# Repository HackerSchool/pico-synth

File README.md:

# pico-synth
The Pico-Synth Board v0.1 is the first version of a Raspberry Pi Pico based synthesizer, featuring an I2S DAC with line-out, a 2x8 switch matrix with individual LEDs, four rotary encoders with switches, an OLED screen, and an SD card slot for optional storage. This fist iteration of the board was designed with a focus on low cost and component availability.

## 📥 1. Clone the Repository & Initialize Submodules

```sh
git clone --recursive https://github.com/HackerSchool/pico-synth.git
cd pico-synth
```

If you already cloned without `--recursive`, initialize submodules manually:

```sh
git submodule update --init --recursive
```

## 📦 2. Install the Pico SDK and Pico Extras

### **Option 1: Install via Raspberry Pi Repo (Recommended on Raspberry Pi OS)**
```sh
sudo apt install cmake gcc-arm-none-eabi libnewlib-arm-none-eabi build-essential
```

### **Option 2: Manually Install (For Other Linux/Windows/macOS)**
#### **Clone & Set Up the Pico SDK**
```sh
mkdir -p ~/pico && cd ~/pico
git clone --recursive https://github.com/raspberrypi/pico-sdk.git
cd pico-sdk
git submodule update --init
```

#### **Clone & Set Up Pico Extras**
```sh
cd ~/pico
git clone --recursive https://github.com/raspberrypi/pico-extras.git
```

## 🌍 3. Set Environment Variables (Each Terminal Session)

Before building, set the paths so CMake can find the SDK and extras:

```sh
export PICO_SDK_PATH=~/pico/pico-sdk
export PICO_EXTRAS_PATH=~/pico/pico-extras
```

To make this **permanent**, add these lines to `~/.bashrc` or `~/.zshrc`:

```sh
echo 'export PICO_SDK_PATH=~/pico/pico-sdk' >> ~/.bashrc
echo 'export PICO_EXTRAS_PATH=~/pico/pico-extras' >> ~/.bashrc
source ~/.bashrc
```

## 🛠 4. Build the Project

1. **Create a Build Directory**
```sh
mkdir -p build && cd build
```

2. **Run CMake to Configure the Build**
```sh
cmake ..
```
if using ninja on windows:
```sh
cmake -G "Ninja" ..
```
3. **Compile the Code**
```sh
make -j$(nproc)
```
if using ninja on windows:
```sh
ninja
```
## 🔥 5. Flash to the Raspberry Pi Pico

### **Step 1: Put the Pico in Bootloader Mode**
- Hold down the **BOOTSEL** button on the Pico.
- Plug it into your computer via **USB**.
- It should appear as a **USB mass storage device** (RPI-RP2).

### **Step 2: Copy the `.uf2` Binary to the Pico**

Once built, the `pico-synth` binary (`.uf2` file) will be in `build/`:
```sh
cp build/pico-synth.uf2 /media/$USER/RPI-RP2/
```

The Pico will automatically reboot and start running the synthesizer!

---

## 🛠 Troubleshooting

- **"pico_sdk_import.cmake not found" error?**
  - Make sure `PICO_SDK_PATH` is set correctly.
  - Try running `source ~/.bashrc`.

- **No `*.uf2` file after `make`?**
  - Check the build log for errors.
  - Ensure `pico_enable_stdio_usb(${bin_name} 1)` is set in `CMakeLists.txt`.

---

## 📜 License
[GPLV3 License](LICENSE)

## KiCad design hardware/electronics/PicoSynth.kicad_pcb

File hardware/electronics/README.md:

# Pico Synth Hardware

The Pico-Synth Board v0.1 is the first version of the synthesizer, featuring a DAC with line-out, a 4x4 switch matrix with individual LEDs, four rotary encoders with switches, an OLED screen, and an SD card slot for optional storage. This fist iteration of the board was designed with a focus on low cost and component availability.

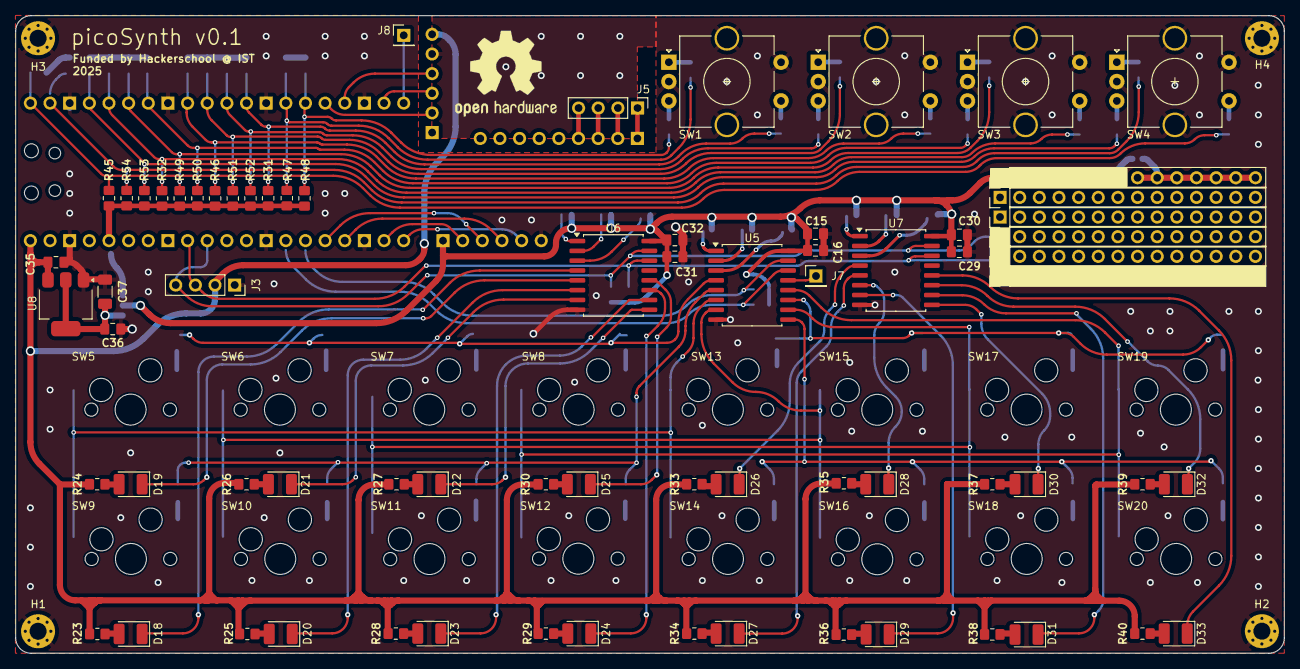
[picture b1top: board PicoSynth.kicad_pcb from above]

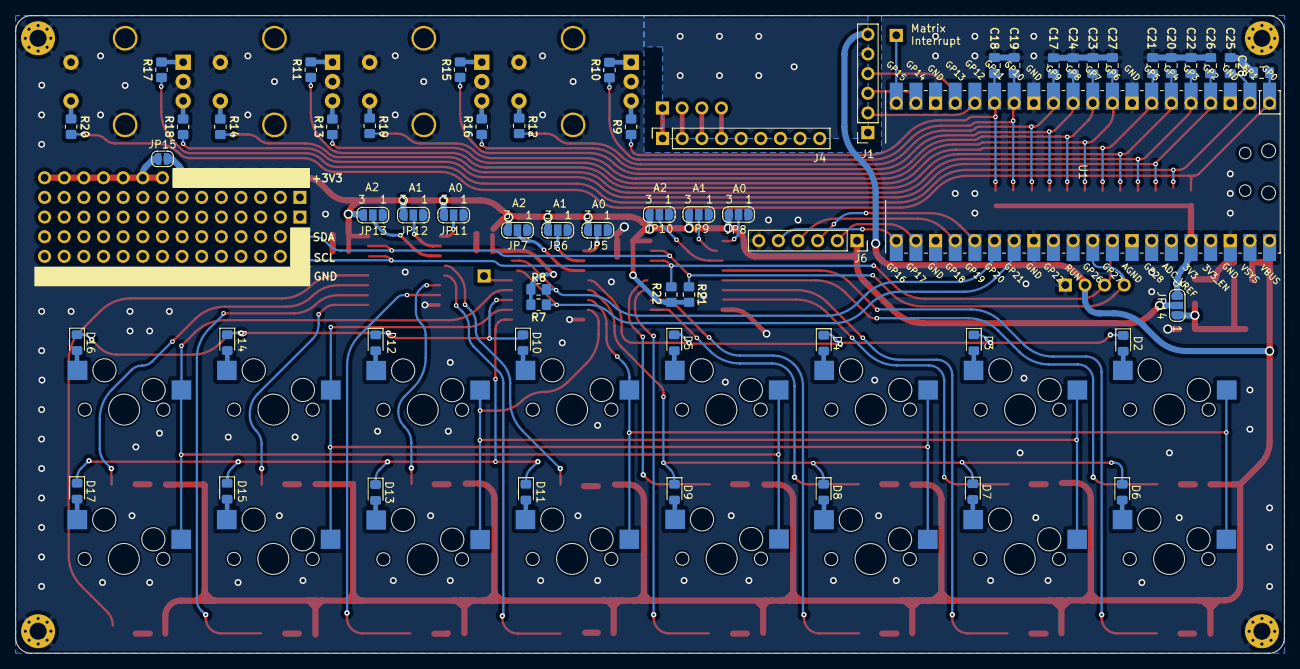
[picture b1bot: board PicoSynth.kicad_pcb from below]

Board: 2 copper layers, 164.0 x 82.4 mm, 150 parts (59 on the bottom side), 112 nets.

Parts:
C15, C17, C18, C19, C20, C21, C22, C23, C24, C25, C26, C27, C28, C30, C32, C36: 100nF; C_0805_2012Metric_Pad1.18x1.45mm_HandSolder_modif
C16, C29, C31, C35: 2.2uF; C_0805_2012Metric_Pad1.18x1.45mm_HandSolder_modif
C37: 10uF; C_1206_3216Metric_Pad1.33x1.80mm_HandSolder_modif
D2, D3, D4, D5, D6, D7, D8, D9, D10, D11, D12, D13, D14, D15, D16, D17: 1N4148WS; D_0805_2012Metric_Pad1.15x1.40mm_HandSolder
D18, D19, D20, D21, D22, D23, D24, D25, D26, D27, D28, D29, D30, D31, D32, D33: LED; LED_1210_3225Metric_Pad1.42x2.65mm_HandSolder
H1, H2, H3, H4: MountingHole_Pad; MountingHole_2.2mm_M2_Pad_Via
J1, J6: Conn_01x06_Socket; PinSocket_1x06_P2.54mm_Vertical
J3: Conn_01x04_Socket; PinSocket_1x04_P2.54mm_Vertical
J4: Conn_01x09_Socket; PinSocket_1x09_P2.54mm_Vertical
J5: Line_Out; PinHeader_1x04_P2.54mm_Vertical
J7, J8: Conn_01x01_Socket; PinHeader_1x01_P2.54mm_Vertical
J9, J10, J11, J12, J13, J14: Conn_01x14_Socket; PinHeader_1x14_P2.54mm_Vertical
JP5, JP8, JP11: A0_Jumper; SolderJumper-3_P1.3mm_Open_RoundedPad1.0x1.5mm_NumberLabels
JP6, JP9, JP12: A1_Jumper; SolderJumper-3_P1.3mm_Open_RoundedPad1.0x1.5mm_NumberLabels
JP7, JP10, JP13, JP14: A2_Jumper; SolderJumper-3_P1.3mm_Open_RoundedPad1.0x1.5mm_NumberLabels
JP15: SolderJumper_2_Open; SolderJumper-2_P1.3mm_Open_RoundedPad1.0x1.5mm
R7, R8, R21, R22: 4.7k; R_0805_2012Metric_Pad1.20x1.40mm_HandSolder_modif
R9, R10, R11, R12, R13, R14, R15, R16, R17, R18, R19, R20, R23, R24, R25, R26, R27, R28, R29, R30, R33, R34, R35, R36, R37, R38, R39, R40: 1k; R_0805_2012Metric_Pad1.20x1.40mm_HandSolder_modif
R31, R32, R45, R46, R47, R48, R49, R50, R51, R52, R53, R54: 10k; R_0805_2012Metric_Pad1.20x1.40mm_HandSolder_modif
SW1, SW2, SW3, SW4: RotaryEncoder_Switch_MP; RotaryEncoder_Alps_EC11E-Switch_Vertical_H20mm_CircularMoun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
SW5, SW6, SW7, SW8, SW9, SW10, SW11, SW12, SW13, SW14, SW15, SW16, SW17, SW18, SW19, SW20: SW_Push_45deg; Cherry-MX_PCB-Mounted_LTST-A683CEGBW_Kailh_Socket_modif
U1: Pico; RPi_Pico_SMD_TH_No_Debug
U5, U6, U7: PCF8574; SOIC-16W_7.5x10.3mm_P1.27mm
U8: AMS1117-3.3; SOT-223-3_TabPin2

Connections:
/+3V3: C15.1, C16.1, C29.1, C30.1, C31.1, C32.1, J6.1, J9.1, J9.2, J9.3, J9.4, J9.5, J9.6, J9.7, JP5.3 (B), JP6.3 (B), JP7.3 (B), JP8.3 (B), JP9.3 (B), JP10.3 (B), JP11.3 (B), JP12.3 (B), JP13.3 (B), JP14.2 (C), JP15.1 (A), R7.1, R8.1, R21.1, R22.1, U5.16 (VDD), U6.16 (VDD), U7.16 (VDD)
/+3V3_Pico: JP14.3 (B), R31.2, R32.2, R45.2, R46.2, R47.2, R48.2, R49.2, R50.2, R51.2, R52.2, R53.2, R54.2, U1.36 (3V3)
/+3V3_Regulator: C36.1, C37.1, JP14.1 (A), U8.2 (VO)
/+5V: C35.1, J1.6, J3.2, R23.1, R24.1, R25.1, R26.1, R27.1, R28.1, R29.1, R30.1, R33.1, R34.1, R35.1, R36.1, R37.1, R38.1, R39.1, R40.1, U1.40 (VBUS), U8.3 (VI)
/BCK: J1.2, U1.16 (GPIO12)
/CLK: J6.4, U1.24 (GPIO18)
/CS: J6.2, U1.22 (GPIO17)
/DIN: J1.3, U1.19 (GPIO14)
/Encoder0_A: C19.1, R10.1, R47.1, U1.14 (GPIO10)
/Encoder0_B: C18.1, R9.1, R48.1, U1.15 (GPIO11)
/Encoder0_Sw: C17.1, R12.2, R31.1, U1.12 (GPIO9)
/Encoder1_A: C23.1, R15.1, R51.1, U1.10 (GPIO7)
/Encoder1_B: C24.1, R16.1, R52.1, U1.11 (GPIO8)
/Encoder1_Sw: C27.1, R19.2, R46.1, U1.9 (GPIO6)
/Encoder2_A: C20.1, R11.1, R49.1, U1.6 (GPIO4)
/Encoder2_B: C21.1, R13.1, R50.1, U1.7 (GPIO5)
/Encoder2_Sw: C22.1, R14.2, R32.1, U1.5 (GPIO3)
/Encoder3_A: C25.1, R17.1, R54.1, U1.2 (GPIO1)
/Encoder3_B: C26.1, R18.1, R53.1, U1.4 (GPIO2)
/Encoder3_Sw: C28.1, R20.2, R45.1, U1.1 (GPIO0)
/G_L: J4.2, J5.2
/G_R: J4.4, J5.4
/L: J4.1, J5.1
/LED_Pin0: D18.1 (K), U6.4 (P0)
/LED_Pin1: D19.1 (K), U6.5 (P1)
/LED_Pin2: D20.1 (K), U6.6 (P2)
/LED_Pin3: D21.1 (K), U6.7 (P3)
/LED_Pin4: D22.1 (K), U6.9 (P4)
/LED_Pin5: D23.1 (K), U6.10 (P5)
/LED_Pin6: D24.1 (K), U6.11 (P6)
/LED_Pin7: D25.1 (K), U6.12 (P7)
/LED_Pin8: D26.1 (K), U7.4 (P0)
/LED_Pin9: D27.1 (K), U7.5 (P1)
/LED_Pin10: D28.1 (K), U7.6 (P2)
/LED_Pin11: D29.1 (K), U7.7 (P3)
/LED_Pin12: D30.1 (K), U7.9 (P4)
/LED_Pin13: D31.1 (K), U7.10 (P5)
/LED_Pin14: D32.1 (K), U7.11 (P6)
/LED_Pin15: D33.1 (K), U7.12 (P7)
/LRCK: J1.4, U1.17 (GPIO13)
/MISO: J6.5, U1.21 (GPIO16)
/MOSI: J6.3, U1.25 (GPIO19)
/Pin0: D2.1 (K), D3.1 (K), D4.1 (K), D5.1 (K), U5.4 (P0)
/Pin1: D6.1 (K), D7.1 (K), D8.1 (K), D9.1 (K), U5.5 (P1)
/Pin2: SW5.1, SW9.1, SW13.1, SW14.1, U5.6 (P2)
/Pin3: SW6.1, SW10.1, SW15.1, SW16.1, U5.7 (P3)
/Pin4: D11.1 (K), D13.1 (K), D15.1 (K), D17.1 (K), U5.9 (P4)
/Pin5: SW7.1, SW11.1, SW17.1, SW18.1, U5.10 (P5)
/Pin6: D10.1 (K), D12.1 (K), D14.1 (K), D16.1 (K), U5.11 (P6)
/Pin7: SW8.1, SW12.1, SW19.1, SW20.1, U5.12 (P7)
/R: J4.3, J5.3
/SCL_Bus_0: R7.2, U1.27 (GPIO21), U5.14 (SCL)
/SCL_Bus_1: J3.3, J11.1, R22.2, U1.32 (GPIO27_ADC1), U6.14 (SCL), U7.14 (SCL)
/SDA_Bus_0: R8.2, U1.26 (GPIO20), U5.15 (SDA)
/SDA_Bus_1: J3.4, J12.1, R21.2, U1.31 (GPIO26_ADC0), U6.15 (SDA), U7.15 (SDA)
/Switch_Interrupt: J8.1, U1.20 (GPIO15)
GND: C15.2, C16.2, C17.2, C18.2, C19.2, C20.2, C21.2, C22.2, C23.2, C24.2, C25.2, C26.2, C27.2, C28.2, C29.2, C30.2, C31.2, C32.2, C35.2, C36.2, C37.2, H1.1, H2.1, H3.1, H4.1, J1.5, J3.1, J6.6, J10.1, J10.2, J10.3, J10.4, J10.5, J10.6, J10.7, J10.8, J10.9, J10.10, J10.11, J10.12, J10.13, J10.14, JP5.1 (A), JP6.1 (A), JP7.1 (A), JP8.1 (A), JP9.1 (A), JP10.1 (A), JP11.1 (A), JP12.1 (A), JP13.1 (A), SW1.C, SW1.MP, SW1.S2, SW2.C, SW2.MP, SW2.S2, SW3.C, SW3.MP, SW3.S2, SW4.C, SW4.MP, SW4.S2, U1.3 (GND), U1.8 (GND), U1.13 (GND), U1.18 (GND), U1.23 (GND), U1.28 (GND), U1.38 (GND), U5.8 (VSS), U6.8 (VSS), U7.8 (VSS), U8.1 (GND)
unnamed: D2.2 (A), SW5.2
unnamed: D3.2 (A), SW6.2
unnamed: D4.2 (A), SW7.2
unnamed: D5.2 (A), SW8.2
unnamed: D6.2 (A), SW9.2
unnamed: D7.2 (A), SW10.2
unnamed: D8.2 (A), SW11.2
unnamed: D9.2 (A), SW12.2
unnamed: D10.2 (A), SW13.2
unnamed: D11.2 (A), SW14.2
unnamed: D12.2 (A), SW15.2
unnamed: D13.2 (A), SW16.2
unnamed: D14.2 (A), SW17.2
unnamed: D15.2 (A), SW18.2
unnamed: D16.2 (A), SW19.2
unnamed: D17.2 (A), SW20.2
unnamed: D18.2 (A), R23.2
unnamed: D19.2 (A), R24.2
unnamed: D20.2 (A), R25.2
unnamed: D21.2 (A), R26.2
unnamed: D22.2 (A), R27.2
unnamed: D23.2 (A), R28.2
unnamed: D24.2 (A), R29.2
unnamed: D25.2 (A), R30.2
unnamed: D26.2 (A), R33.2
unnamed: D27.2 (A), R34.2
unnamed: D28.2 (A), R35.2
unnamed: D29.2 (A), R36.2
unnamed: D30.2 (A), R37.2
unnamed: D31.2 (A), R38.2
unnamed: D32.2 (A), R39.2
unnamed: D33.2 (A), R40.2
unnamed: J7.1, U5.13 (~INT)
unnamed: J9.8, J9.9, J9.10, J9.11, J9.12, J9.13, J9.14, JP15.2 (B)
unnamed: JP5.2 (C), U5.1 (A0)
unnamed: JP6.2 (C), U5.2 (A1)
unnamed: JP7.2 (C), U5.3 (A2)
unnamed: JP8.2 (C), U6.1 (A0)
unnamed: JP9.2 (C), U6.2 (A1)
unnamed: JP10.2 (C), U6.3 (A2)
unnamed: JP11.2 (C), U7.1 (A0)
unnamed: JP12.2 (C), U7.2 (A1)
unnamed: JP13.2 (C), U7.3 (A2)
unnamed: R9.2, SW1.B
unnamed: R10.2, SW1.A
unnamed: R11.2, SW3.A
unnamed: R12.1, SW1.S1
unnamed: R13.2, SW3.B
unnamed: R14.1, SW3.S1
unnamed: R15.2, SW2.A
unnamed: R16.2, SW2.B
unnamed: R17.2, SW4.A
unnamed: R18.2, SW4.B
unnamed: R19.1, SW2.S1
unnamed: R20.1, SW4.S1

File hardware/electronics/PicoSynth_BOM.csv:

Reference;Value;Datasheet;Footprint;Qty;DNP
;;;;;
;;;;;
;;;;;
C15,C17,C18,C19,C20,C21,C22,C23,C24,C25,C26,C27,C28,C30,C32,C36;100nF;~;Cern_Ignition:C_0805_2012Metric_Pad1.18x1.45mm_HandSolder_modif;16;
C16,C29,C31,C35;2.2uF;~;Cern_Ignition:C_0805_2012Metric_Pad1.18x1.45mm_HandSolder_modif;4;
C37;10uF;~;Cern_Ignition:C_1206_3216Metric_Pad1.33x1.80mm_HandSolder_modif;1;
;;;;;
D2,D3,D4,D5,D6,D7,D8,D9,D10,D11,D12,D13,D14,D15,D16,D17;1N4148WS;https://www.vishay.com/docs/85751/1n4148ws.pdf;Diode_SMD:D_0805_2012Metric_Pad1.15x1.40mm_HandSolder;16;
D18,D19,D20,D21,D22,D23,D24,D25,D26,D27,D28,D29,D30,D31,D32,D33;LED;~;LED_SMD:LED_1210_3225Metric_Pad1.42x2.65mm_HandSolder;16;
J1,J6;Conn_01x06_Socket;~;Connector_PinSocket_2.54mm:PinSocket_1x06_P2.54mm_Vertical;2;
J3;Conn_01x04_Socket;~;Connector_PinSocket_2.54mm:PinSocket_1x04_P2.54mm_Vertical;1;
J4;Conn_01x09_Socket;~;Connector_PinSocket_2.54mm:PinSocket_1x09_P2.54mm_Vertical;1;
J5;Line_Out;~;Connector_PinHeader_2.54mm:PinHeader_1x04_P2.54mm_Vertical;1;
J7,J8;Conn_01x01_Socket;~;Connector_PinHeader_2.54mm:PinHeader_1x01_P2.54mm_Vertical;2;
J9,J10,J11,J12,J13,J14;Conn_01x14_Socket;~;Connector_PinHeader_2.54mm:PinHeader_1x14_P2.54mm_Vertical;6;
JP5,JP8,JP11;A0_Jumper;~;Jumper:SolderJumper-3_P1.3mm_Open_RoundedPad1.0x1.5mm_NumberLabels;3;
JP6,JP9,JP12;A1_Jumper;~;Jumper:SolderJumper-3_P1.3mm_Open_RoundedPad1.0x1.5mm_NumberLabels;3;
JP7,JP10,JP13,JP14;A2_Jumper;~;Jumper:SolderJumper-3_P1.3mm_Open_RoundedPad1.0x1.5mm_NumberLabels;4;
;;;;;
;;;;;
;;;;;
R7,R8,R21,R22;4.7k;~;Cern_Ignition:R_0805_2012Metric_Pad1.20x1.40mm_HandSolder_modif;4;
R9,R10,R11,R12,R13,R14,R15,R16,R17,R18,R19,R20,R23,R24,R25,R26,R27,R28,R29,R30,R33,R34,R35,R36,R37,R38,R39,R40;1k;~;Cern_Ignition:R_0805_2012Metric_Pad1.20x1.40mm_HandSolder_modif;28;
R31,R32,R45,R46,R47,R48,R49,R50,R51,R52,R53,R54;10k;~;Cern_Ignition:R_0805_2012Metric_Pad1.20x1.40mm_HandSolder_modif;12;
SW1,SW2,SW3,SW4;RotaryEncoder_Switch_MP;~;Lame_Lib:RotaryEncoder_Alps_EC11E-Switch_Vertical_H20mm_CircularMountingHoles;4;
SW5,SW6,SW7,SW8,SW9,SW10,SW11,SW12,SW13,SW14,SW15,SW16,SW17,SW18,SW19,SW20;SW_Push_45deg;~;Cherry_MX_switches:Cherry-MX_PCB-Mounted_LTST-A683CEGBW_Kailh_Socket_modif;16;
U1;Pico;;Pi_Pico:RPi_Pico_SMD_TH_No_Debug;1;
;;;;;
;;;;;
U5,U6,U7;PCF8574;http://www.nxp.com/docs/en/data-sheet/PCF8574_PCF8574A.pdf;Package_SO:SOIC-16W_7.5x10.3mm_P1.27mm;3;
U8;AMS1117-3.3;http://www.advanced-monolithic.com/pdf/ds1117.pdf;Package_TO_SOT_SMD:SOT-223-3_TabPin2;1;

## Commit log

2025-03-14 some formating
2025-03-15 Staring the schematics in Kicad, DAC schematics completed with better LDO regulators
2025-03-15 Added some spice simulations i did in january for the analog low pass filter
2025-03-15 comp time wavetables
2025-03-15 add: oscilator
2025-03-16 add: oscillator working!
2025-03-16 add: adsrenvelope
2025-03-16 Some work on the simulation, filter is working but headphone driver not
2025-03-17 tinyusb midi + cdc
2025-03-17 add: midi over usb
2025-03-17 del: tinyusb submodule
2025-03-18 add: synth work in progress
2025-03-18 multivoice: not optimized, max 2-3
2025-03-18 add: osc no floats, only fixed baby
2025-03-18 A lot of updates in the Schematic... To-Do: hot swaps in switches, SD card and I2C for screen
2025-03-18 add: polyphony! fixed point ftw!
2025-03-18 fix: adsr discontinuity
2025-03-19 SD card and i2c for display added, starting some component placement
2025-03-19 New horizontal layout
2025-03-20 add: filter test, sinc LUT and fixed_point header
2025-03-20 Low pass baby
2025-03-20 Low pass coef working, convolution is fucked
2025-03-20 Envelope fixed point math w/ header
2025-03-20 cheby filter 16 bit on the way
2025-03-21 Cheby Coefs baby
2025-03-21 cheby test, lord have mercy
2025-03-21 add: cheby things
2025-03-21 cheby kinda, need to figure out the output
2025-03-21 cheby a funfar, cuttoff entre 3-10khz
2025-03-23 This layout could work, need to ponder
2025-03-23 Deleted some unused files
2025-03-25 Basic routing almost complete: 6 more traces to go
2025-03-30 Routing Done, to-do: verify schematic and fix silkscreen
2025-03-30 Added schematic PDF
2025-03-31 TO-DO: fix silkscreen
2025-04-01 Finished layout, no errors in DRC, silkscreen aso finished
2025-04-02 Added bill of materials
2025-04-15 Ready to order
2025-04-15 Fix readme
2025-05-02 Added bill of materials with link for the first prototypes
2025-05-02 File fixes
2025-05-02 Images et al
2025-05-09 ssd1306 added flip and rotate and all that
2025-05-09 midi notes on screen
2025-05-10 Create a hardware tester script in micropython
2025-05-15 switches and LEDS baby
2025-05-15 encoders baby
2025-05-15 keys to note
2025-05-15 config.h
2025-05-17 encoder to change the wave-type
2025-05-18 hardware class but not good
2025-05-18 hardware class working
2025-05-18 ADSR encoder
2025-05-18 Filter Encoder
2025-05-19 Added some 3D models, .stl because .step are too large
2025-06-07 hardware encoder polling
2025-06-07 midi notes out
2025-06-08 fix: out of tune (and overclock a little bit more)
2025-06-08 midi / swiches flow menu
2025-06-08 sequencer start
2025-06-08 sequencer hardware interrupts
2025-06-08 sequencer hardware interrupts and menu baby
2025-06-08 sequencer baby steps
2025-06-09 SD card tester
2025-06-09 Fixing my mistakes, bad git user ig
2025-06-09 Still fixing mistakes
2025-06-10 updates?
2025-06-10 interpolator for osc LUT read
2025-06-10 How to ninja on windows
2025-06-11 cleanup main
2025-06-11 DUAL CORE BABY
2025-06-11 cleanup sequencer dual core
2025-06-11 envelope uint8 steps
2025-06-11 foda-se
2025-06-11 cleanup ui, still missing integration
2025-06-11 cleanup midi-handler
2025-06-11 git modules
2025-06-11 envelopes by midi
2025-06-11 cleanup
2025-06-11 synth finnally working right
2025-06-11 octave changer
2025-06-12 sequencer fix: pause and add channel
2025-06-12 sequencer edit note menu
2025-06-13 adsr per channel
2025-06-13 adsr LUT linear feeling
2025-06-13 midi filter, other bug fixes
2025-06-14 start FM synth
2025-06-16 cmake
2025-06-16 I2s pin definitions
2025-06-16 test
2025-06-16 case v0.4
2025-06-16 ui fixed sequencer refresh
2025-06-17 osc and envelope in place buffer
2025-06-18 Add TinyUSB as submodule
2025-06-18 ODEIO WINDOWS PUTA QUE O PARIU OS DE MERDA
2025-06-18 rm tinyusb, wasnt its fault
2025-06-18 voices and operators
2025-06-19 To be able to pull
2025-06-19 The choose menu
2025-06-19 New choose state manu
2025-06-19 rebase
2025-06-19 sampler into switches and sequencer
2025-06-19 fix: sampler pop (correct header read)
2025-06-19 sd card sampler buffer
2025-06-19 Wavetable display et al
2025-06-20 usb mass storage
2025-06-20 Sampler Menu start
2025-06-20 Reading sample names not working yet
2025-06-20 rebase for the sampler menu
2025-06-20 patches start
2025-06-20 fm edit menu
2025-06-21 fm edit menu, switches back to main
2025-06-21 Bug fixes in the choose menu
2025-06-22 Made a basic Delay ay ay ª' ª'
2025-06-22 Removed safety limit
2025-06-23 Bug Fixes
2025-06-23 Improved the Choose Menu usability
2026-04-03 Compiles for the Pico 2, added some effects (work in progress)
2026-04-06 Better effect
2026-04-06 Added a Karplus-Strong Engine, also some new cool bitmaps
2026-04-07 Added a new modal synthesis engine
2026-04-08 Added an Analog menu for some variation
2026-04-08 Bug fixes and Presets!
2026-04-14 Added LFO, Reduced RAM usage overall, better sample playback, bug fixes
